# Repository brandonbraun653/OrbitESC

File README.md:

# OrbitESC

Brushless motor controller development environment for STM32-based ESC firmware, a host-side simulator, and a Python GUI/tooling suite.

## Features

- Field-oriented control (FOC)-centric ESC stack with FreeRTOS integration
- STM32F446RE target (embedded) and host simulator build (ChimeraSim)
- Protobuf/Nanopb command and telemetry schema for C/C++ and Python
- Python tools and PyQt5 GUI for monitoring, configuration, and testing
- OrbitCommand: Qt 6/QML C++ desktop console with dark-neon HUD, live plotting, and parameter editing
- CMake presets for embedded and simulator builds

## Project Structure

| Path | Description |
| --- | --- |
| `src/` | C++ sources for firmware, simulator integration, startup, tasks, and libraries. |
| `lib/` | Third-party and in-tree libraries: Aurora, Chimera, ChimeraSim, CMSIS, FreeRTOS, Thor, tinyusb, db. |
| `pyorbit/` | Python package for host tools, GUI (`pyorbit/app`), serial/CAN clients, protobuf stubs. |
| `tools/OrbitCommand/` | Standalone Qt 6/QML C++ desktop console for USB serial, simulator TCP, monitoring, and parameter editing. |
| `scripts/` | Helper scripts: build embedded, generate protobufs, CAN interface setup. |
| `model/` | MATLAB/Simulink models and notebooks related to control algorithms. |
| `CMakePresets.json` | Configure/build presets for embedded and simulator targets. |

---

## Quickstart (Python tooling & GUI)

This repo uses `uv` for Python dependency management. Python 3.11 is required and auto-detected from `pyproject.toml`.

1) Create and sync the environment
```bash
uv venv
uv sync
```

2) Option A: Activate the environment
```bash
source .venv/bin/activate
```

2) Option B: Run one-off commands without activation
```bash
uv run <command>
```

3) Launch the GUI
```bash
uv run python -m pyorbit.app.main
```

Common tasks
```bash
# Run unit tests
uv run pytest

# Type check
uv run mypy

# Lint / Format
uv run flake8
uv run black .
```

Development workflow
- **Add dependencies**: `uv add <package>`
- **Sync/update**: `uv sync`
- **Update lockfile**: `uv lock`

---

## Protobuf/Nanopb workflow

Protobuf definitions live under `src/core/com/proto`. C bindings are generated with Nanopb for the firmware, and Python stubs for `pyorbit`.

Prerequisites
- `protoc` available in PATH
- The repo includes the Nanopb generator under `lib/Aurora/lib/nanopb/...`

Generate all bindings
```bash
cd scripts
./build_proto.sh
```

What it does
- Runs Nanopb to generate C/C++ descriptors into `src/core/com/proto`
- Runs `protoc` to generate Python modules and `.pyi` into `pyorbit/nanopb`

---

## OrbitCommand (Qt 6/QML C++ console)

OrbitCommand is the C++ desktop replacement path for the PyQt GUI. It lives in `tools/OrbitCommand` as a standalone CMake project so it never enters the ARM firmware build.

Build and run:

```bash
cd tools/OrbitCommand
cmake --preset release
cmake --build --preset release
./build/release/OrbitCommand
```

Test all tiers (unit, real-simulator system tests, and Qat GUI E2E):

```bash
uv sync
cmake --preset "OrbitESC Simulator Release"   # from the repository root
cmake --build --preset "OrbitESC Simulator Release"
cd tools/OrbitCommand
cmake --preset release
cmake --build --preset release
ctest --preset release --output-on-failure
```

The system and GUI tiers skip cleanly when the simulator, `qat`, or a display is unavailable. `scripts/test_orbitcommand.sh` wraps the common combinations. See `tools/OrbitCommand/README.md` for prerequisites, test tiers, the Qat object-name contract, protocol notes, simulator connection, and V0 limitations.

---

## Embedded firmware build (STM32F446RE)

The firmware uses CMake presets and GCC ARM toolchain.

Prerequisites
- CMake ≥ 3.16, build-essential toolchain
- Arm GNU Toolchain `arm-none-eabi-*` (see `scripts/install_arm_gcc.sh` or install from Arm)

Configure & build (Debug)
```bash
cmake --preset "OrbitESC_V3 Debug"
cmake --build --preset "OrbitESC_V3 Debug"
```

Configure & build (Release)
```bash
cmake --preset "OrbitESC_V3 Release"
cmake --build --preset "OrbitESC_V3 Release"
```

Artifacts
- Build directories under `build/debug` and `build/release`
- The `OrbitESC` image and map file are produced; a copy of the image is placed under a `sys_image` folder in the preset's runtime output directory

Flashing
- Flashing is board/debugger dependent (ST-Link, J-Link, OpenOCD). Provide your preferred tool or script; a generic OpenOCD flow is recommended.

---

## Simulator build (host)

Build a host-executable with simulated hardware using ChimeraSim.

Host prerequisites (Ubuntu/Debian)
```bash
sudo apt-get update
sudo apt-get install -y build-essential cmake pkg-config libzmq3-dev
```

Configure & build
```bash
cmake --preset "OrbitESC Simulator"
cmake --build --preset "OrbitESC Simulator"
```

Run
```bash
# Example path; adjust if your CMake generator places binaries differently
./build/sim/OrbitESC
```

---

## CAN bus setup (Linux)

Scripts are provided to bring up a `can0` interface at 1 Mbit/s. Root privileges are required.

Open the CAN port
```bash
sudo ./scripts/open_can_port.sh
```

Close the CAN port
```bash
sudo ./scripts/close_can_port.sh
```

Note: Ensure a compatible CAN adapter/driver is present. The Python side uses `python-can`.

---

## Testing & quality checks

All commands can be run with `uv run ...` without activating the venv.

```bash
# Python tests
uv run pytest -q

# Type checks
uv run mypy

# Linting / formatting
uv run flake8
uv run black --check .
```

Pytest is configured to discover tests under `pyorbit/tests`.

OrbitCommand has separate C++ and GUI test tiers:

```bash
scripts/test_orbitcommand.sh              # unit + system + Qat E2E
scripts/test_orbitcommand.sh --unit-only  # no simulator or display required
```

See `tools/OrbitCommand/README.md` for the full tier list, coverage, and sanitizer presets.

---

## Troubleshooting

- CMake cannot find `arm-none-eabi-gcc`: install the Arm GNU Toolchain and ensure it is in PATH.
- Simulator link fails on `zmq`: install `libzmq3-dev` (or the platform equivalent) and reconfigure.
- `protoc: command not found`: install protobuf compiler (`sudo apt-get install -y protobuf-compiler`).
- GUI fails to start: ensure `PyQt5` is installed (it is declared in `pyproject.toml`), then `uv sync` again.

---

## License

MIT. See `LICENSE`.

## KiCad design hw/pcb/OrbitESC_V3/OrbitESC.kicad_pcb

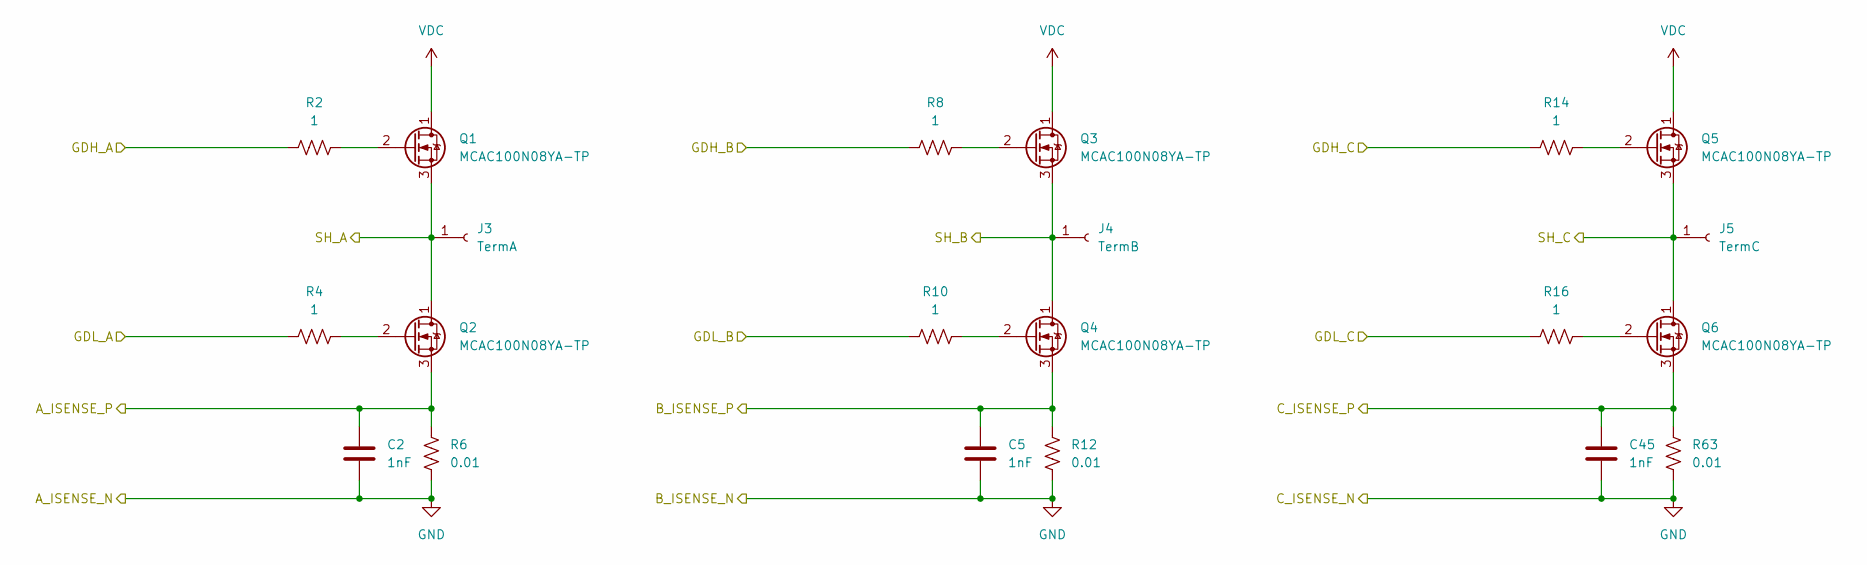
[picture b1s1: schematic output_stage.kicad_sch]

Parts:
C2, C5, C45: 1nF; C_0402_1005Metric; LCSC C1523
J3: TermA; TestPoint_Pad_2.5x2.5mm; DigiKey N/A
J4: TermB; TestPoint_Pad_2.5x2.5mm; DigiKey N/A
J5: TermC; TestPoint_Pad_2.5x2.5mm; DigiKey N/A
Q1, Q2, Q3, Q4, Q5, Q6: MCAC100N08YA-TP; TRANS_BSC076N06NS3-G; DigiKey 353-MCAC100N08YA-TPCT-ND
R2, R4, R8, R10, R14, R16: 1; R_0402_1005Metric; LCSC C25086
R6, R12, R63: 0.01; R_2512_6332Metric; DigiKey CRA2512-FZ-R010ELFCT-ND

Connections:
/Outputs and Shunts/A_ISENSE_P: C2.1, Q2.3 (S), R6.1; also elsewhere on the board
/Outputs and Shunts/B_ISENSE_P: C5.1, Q4.3 (S), R12.1; also elsewhere on the board
/Outputs and Shunts/C_ISENSE_P: C45.1, Q6.3 (S), R63.1; also elsewhere on the board
/Outputs and Shunts/GDH_A: R2.1; also elsewhere on the board
/Outputs and Shunts/GDH_B: R8.1; also elsewhere on the board
/Outputs and Shunts/GDH_C: R14.1; also elsewhere on the board
/Outputs and Shunts/GDL_A: R4.1; also elsewhere on the board
/Outputs and Shunts/GDL_B: R10.1; also elsewhere on the board
/Outputs and Shunts/GDL_C: R16.1; also elsewhere on the board
/Outputs and Shunts/SH_A: J3.1, Q1.3 (S), Q2.1 (D); also elsewhere on the board
/Outputs and Shunts/SH_B: J4.1, Q3.3 (S), Q4.1 (D); also elsewhere on the board
/Outputs and Shunts/SH_C: J5.1, Q5.3 (S), Q6.1 (D); also elsewhere on the board
GND: C2.2, C5.2, C45.2, R6.2, R12.2, R63.2; also elsewhere on the board
unnamed: Q1.2 (G), R2.2
unnamed: Q2.2 (G), R4.2
unnamed: Q3.2 (G), R8.2
unnamed: Q4.2 (G), R10.2
unnamed: Q5.2 (G), R14.2
unnamed: Q6.2 (G), R16.2
VDC: Q1.1 (D), Q3.1 (D), Q5.1 (D); also elsewhere on the board

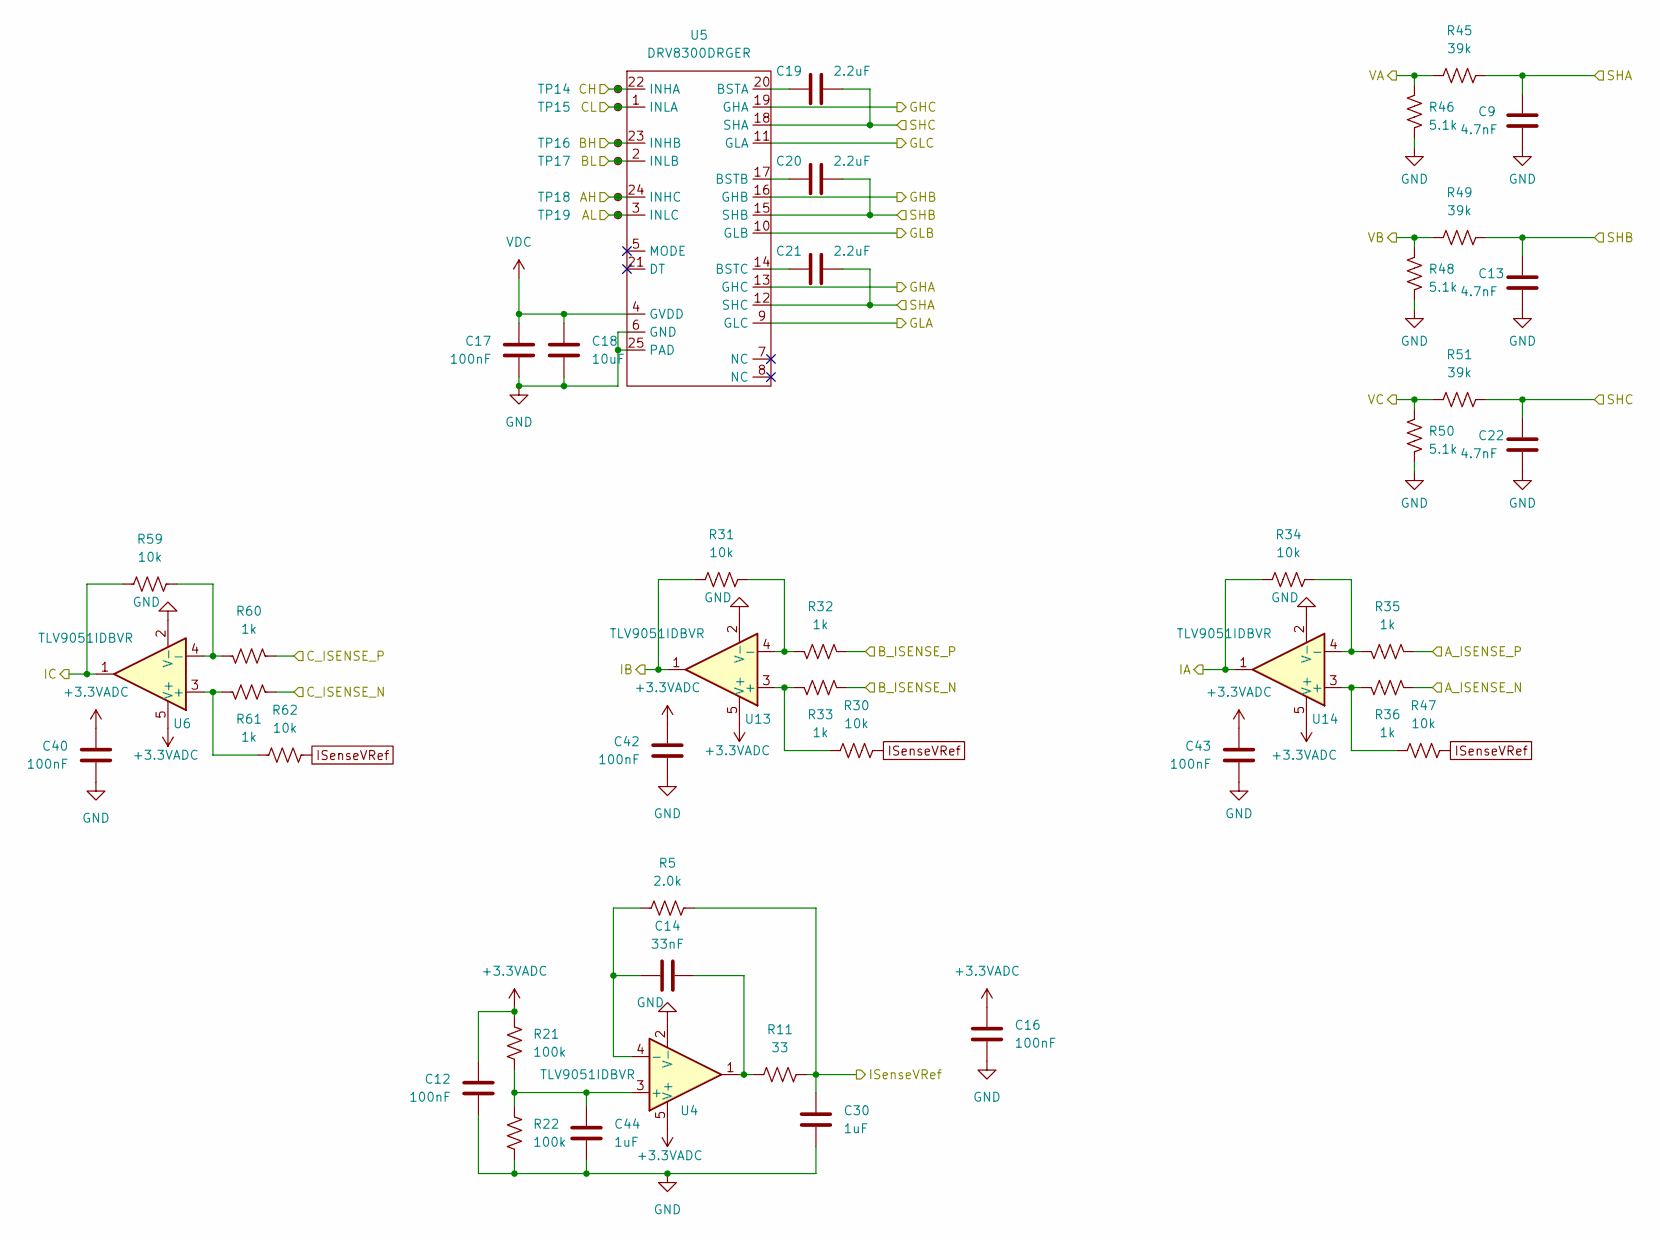
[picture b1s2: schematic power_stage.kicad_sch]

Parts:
C9, C13, C22: 4.7nF; C_0402_1005Metric; LCSC C1538
C12, C16, C17, C40, C42, C43: 100nF; C_0402_1005Metric; LCSC C307331
C14: 33nF; C_0402_1005Metric; LCSC C1585
C18: 10uF; C_0805_2012Metric; LCSC C440198
C19, C20, C21: 2.2uF; C_0805_2012Metric; LCSC C49217
C30, C44: 1uF; C_0402_1005Metric; LCSC C52923
R5: 2.0k; R_0402_1005Metric; LCSC C4109
R11: 33; R_0402_1005Metric; LCSC C25105
R21, R22: 100k; R_0402_1005Metric; LCSC C25741
R30, R31, R34, R47, R59, R62: 10k; R_0402_1005Metric; LCSC C25744
R32, R33, R35, R36, R60, R61: 1k; R_0402_1005Metric; LCSC C11702
R45, R49, R51: 39k; R_0402_1005Metric; LCSC C25783
R46, R48, R50: 5.1k; R_0402_1005Metric; LCSC C25905
TP14: AH; TestPoint_Pad_D1.0mm; DigiKey N/A
TP15: AL; TestPoint_Pad_D1.0mm; DigiKey N/A
TP16: BH; TestPoint_Pad_D1.0mm; DigiKey N/A
TP17: BL; TestPoint_Pad_D1.0mm; DigiKey N/A
TP18: CH; TestPoint_Pad_D1.0mm; DigiKey N/A
TP19: CL; TestPoint_Pad_D1.0mm; DigiKey N/A
U4, U6, U13, U14: TLV9051IDBVR; SOT-23-5; LCSC C1849429
U5: DRV8300DRGER; VQFN-24-1EP_4x4mm_P0.5mm_EP2.45x2.45mm; DigiKey 296-DRV8300DRGERCT-ND

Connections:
+3.3VADC: C12.2, C16.1, C40.1, C42.1, C43.1, R21.2, U4.5 (V+), U6.5 (V+), U13.5 (V+), U14.5 (V+); also elsewhere on the board
/MCU/GATE_DRIVE_AH: TP18.1, U5.24 (INHC); also elsewhere on the board
/MCU/GATE_DRIVE_AL: TP19.1, U5.3 (INLC); also elsewhere on the board
/MCU/GATE_DRIVE_BH: TP16.1, U5.23 (INHB); also elsewhere on the board
/MCU/GATE_DRIVE_BL: TP17.1, U5.2 (INLB); also elsewhere on the board
/MCU/GATE_DRIVE_CH: TP14.1, U5.22 (INHA); also elsewhere on the board
/MCU/GATE_DRIVE_CL: TP15.1, U5.1 (INLA); also elsewhere on the board
/MCU/MOTOR_IA: R34.1, U14.1; also elsewhere on the board
/MCU/MOTOR_IB: R31.1, U13.1; also elsewhere on the board
/MCU/MOTOR_IC: R59.1, U6.1; also elsewhere on the board
/MCU/MOTOR_VA: R45.1, R46.1; also elsewhere on the board
/MCU/MOTOR_VB: R48.1, R49.1; also elsewhere on the board
/MCU/MOTOR_VC: R50.1, R51.1; also elsewhere on the board
/Outputs and Shunts/A_ISENSE_P: R35.1; also elsewhere on the board
/Outputs and Shunts/B_ISENSE_P: R32.1; also elsewhere on the board
/Outputs and Shunts/C_ISENSE_P: R60.1; also elsewhere on the board
/Outputs and Shunts/GDH_A: U5.13 (GHC); also elsewhere on the board
/Outputs and Shunts/GDH_B: U5.16 (GHB); also elsewhere on the board
/Outputs and Shunts/GDH_C: U5.19 (GHA); also elsewhere on the board
/Outputs and Shunts/GDL_A: U5.9 (GLC); also elsewhere on the board
/Outputs and Shunts/GDL_B: U5.10 (GLB); also elsewhere on the board
/Outputs and Shunts/GDL_C: U5.11 (GLA); also elsewhere on the board
/Outputs and Shunts/SH_A: C9.2, C21.2, R45.2, U5.12 (SHC); also elsewhere on the board
/Outputs and Shunts/SH_B: C13.2, C20.2, R49.2, U5.15 (SHB); also elsewhere on the board
/Outputs and Shunts/SH_C: C19.2, C22.2, R51.2, U5.18 (SHA); also elsewhere on the board
GND: C9.1, C12.1, C13.1, C16.2, C17.1, C18.2, C22.1, C30.2, C40.2, C42.2, C43.2, C44.2, R22.1, R33.1, R36.1, R46.2, R48.2, R50.2, R61.1, U4.2 (V-), U5.6 (GND), U5.25 (PAD), U6.2 (V-), U13.2 (V-), U14.2 (V-); also elsewhere on the board
ISenseVRef: C30.1, R5.1, R11.1, R30.2, R47.2, R62.2; also elsewhere on the board
unnamed: C14.2, R11.2, U4.1
unnamed: C44.1, R21.1, R22.2, U4.3 (+)
unnamed: C14.1, R5.2, U4.4 (-)
unnamed: C19.1, U5.20 (BSTA)
unnamed: C20.1, U5.17 (BSTB)
unnamed: C21.1, U5.14 (BSTC)
unnamed: R61.2, R62.1, U6.3 (+)
unnamed: R59.2, R60.2, U6.4 (-)
unnamed: R30.1, R33.2, U13.3 (+)
unnamed: R31.2, R32.2, U13.4 (-)
unnamed: R36.2, R47.1, U14.3 (+)
unnamed: R34.2, R35.2, U14.4 (-)
VDC: C17.2, C18.1, U5.4 (GVDD); also elsewhere on the board

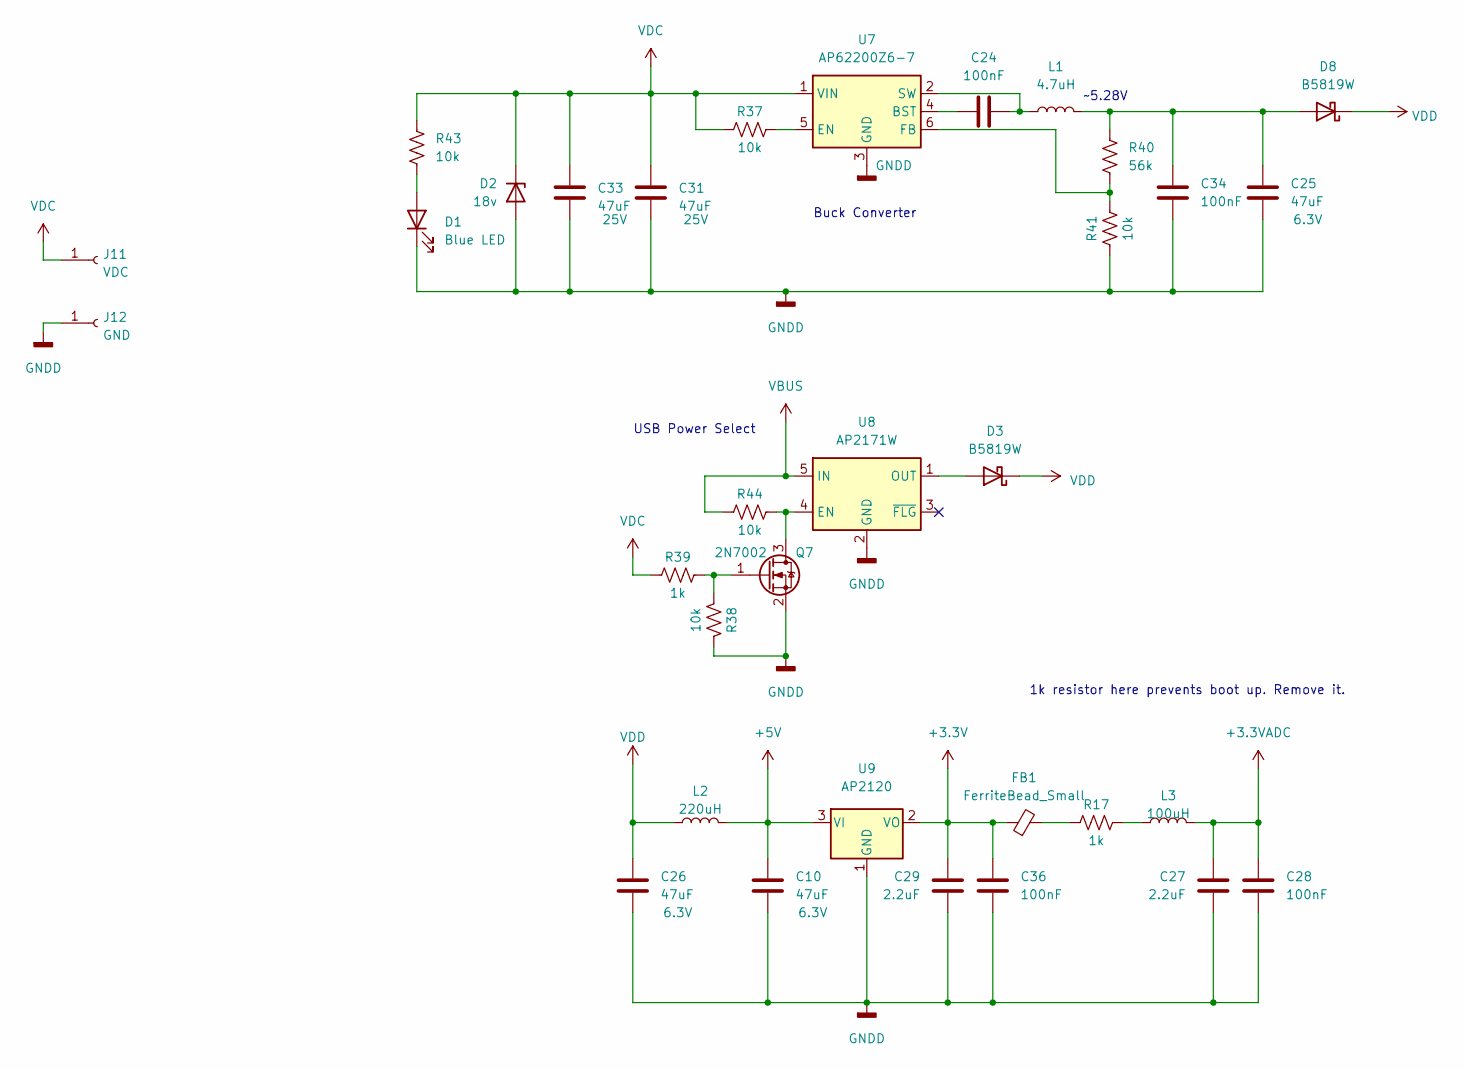
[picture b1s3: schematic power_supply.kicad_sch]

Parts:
C10, C25, C26: 47uF; C_0805_2012Metric; Voltage 6.3V; LCSC C16780
C24, C28, C34, C36: 100nF; C_0402_1005Metric; LCSC C307331
C27, C29: 2.2uF; C_0402_1005Metric; LCSC C12530
C31, C33: 47uF; C_1206_3216Metric; Voltage 25V; DigiKey 445-8047-1-ND
D1: Blue LED; D_0603_1608Metric; LCSC C72041
D2: 18v; D_SMA; DigiKey SMAZ18-FDICT-ND
D3, D8: B5819W; D_SOD-123; LCSC C8598
FB1: FerriteBead_Small; R_0603_1608Metric; LCSC C1002
J11: VDC; TestPoint_Pad_2.5x2.5mm; DigiKey N/A
J12: GND; TestPoint_Pad_2.5x2.5mm; DigiKey N/A
L1: 4.7uH; L_Bourns-SRN6028; DigiKey 587-2100-1-ND
L2: 220uH; L_1812_4532Metric_Pad1.30x3.40mm_HandSolder; DigiKey CM453232-221KLCT-ND
L3: 100uH; L_0805_2012Metric; LCSC C68035
Q7: 2N7002; SOT-23; LCSC C8545
R17, R39: 1k; R_0402_1005Metric; LCSC C11702
R37, R38, R41, R43, R44: 10k; R_0402_1005Metric; LCSC C25744
R40: 56k; R_0402_1005Metric; LCSC C25796
U7: AP62200Z6-7; SOT-563; DigiKey 31-AP62200Z6-7CT-ND
U8: AP2171W; SOT-23-5; DigiKey AP2171WGDICT-ND
U9: AP2120; SOT-23; DigiKey AP2120N-3.3TRG1DICT-ND

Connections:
+3.3V: C29.2, C36.1, FB1.1, U9.2 (VO); also elsewhere on the board
+3.3VADC: C27.2, C28.1, L3.2; also elsewhere on the board
+5V: C10.1, L2.2, U9.3 (VI); also elsewhere on the board
GND: C10.2, C25.2, C26.2, C27.1, C28.2, C29.1, C31.2, C33.2, C34.2, C36.2, D1.1 (K), D2.2 (A), J12.1, Q7.2 (S), R38.1, R41.1, U7.3 (GND), U8.2 (GND), U9.1 (GND); also elsewhere on the board
unnamed: D1.2 (A), R43.2
unnamed: D3.2 (A), U8.1 (OUT)
unnamed: C25.1, C34.1, D8.2 (A), L1.2, R40.1
unnamed: FB1.2, R17.1
unnamed: L3.1, R17.2
unnamed: Q7.3 (D), R44.2, U8.4 (EN)
unnamed: Q7.1 (G), R38.2, R39.2
unnamed: C24.2, U7.4 (BST)
unnamed: R37.2, U7.5 (EN)
unnamed: R40.2, R41.2, U7.6 (FB)
unnamed: C24.1, L1.1, U7.2 (SW)
VBUS: R44.1, U8.5 (IN); also elsewhere on the board
VDC: C31.1, C33.1, D2.1 (K), J11.1, R37.1, R39.1, R43.1, U7.1 (VIN); also elsewhere on the board
VDD: C26.1, D3.1 (K), D8.1 (K), L2.1

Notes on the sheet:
~5.28V
Buck Converter
USB Power Select
1k resistor here prevents boot up. Remove it.

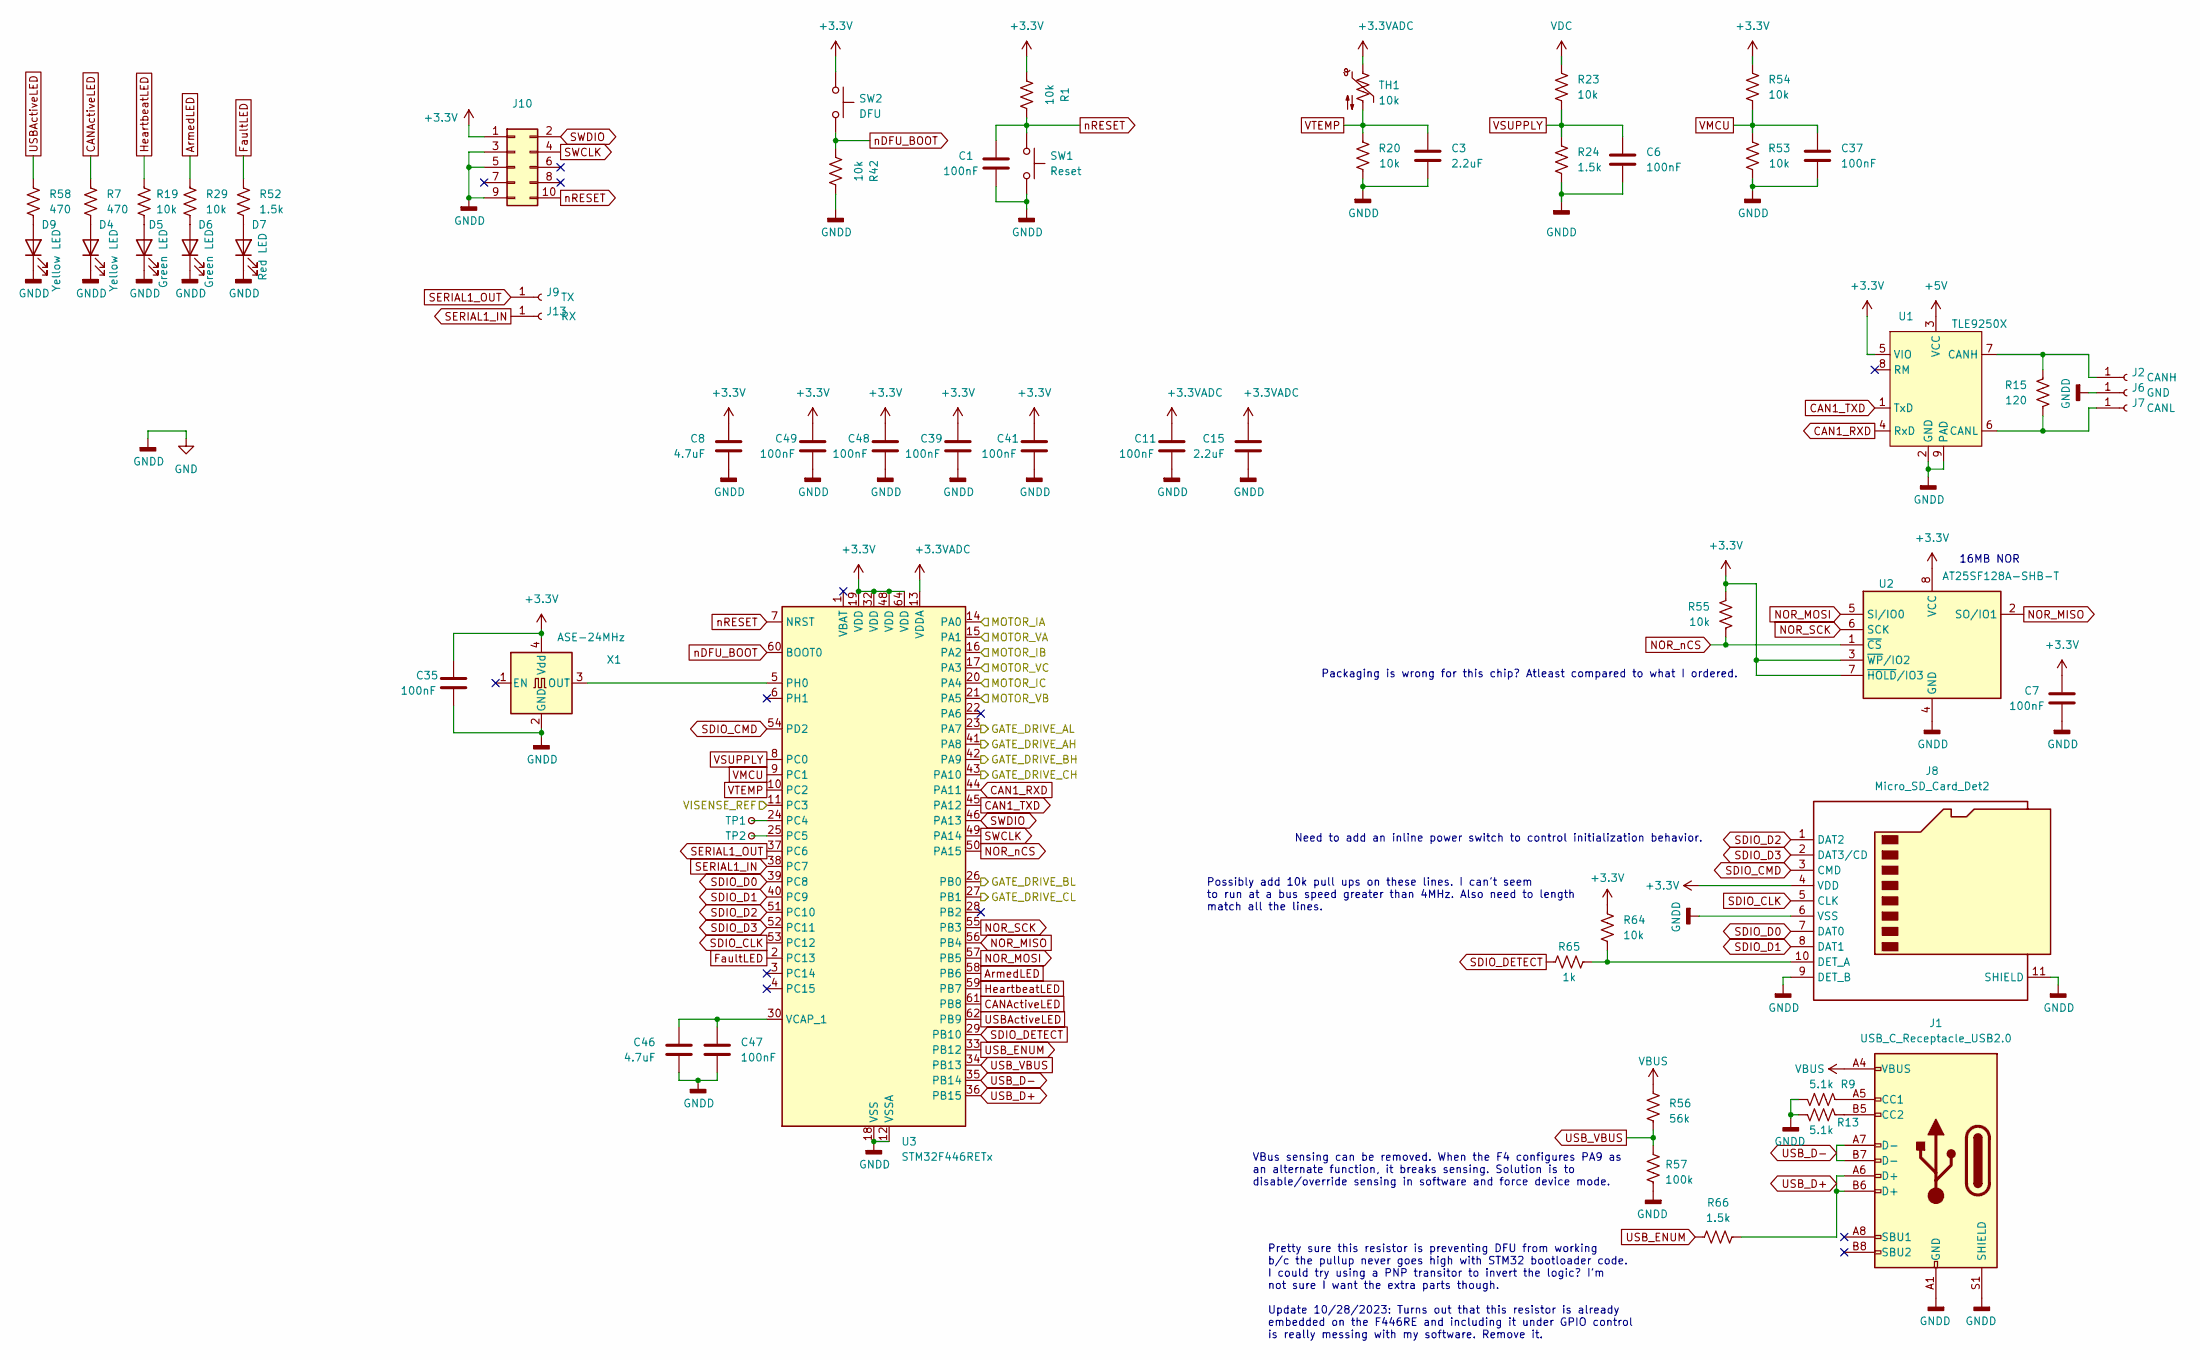
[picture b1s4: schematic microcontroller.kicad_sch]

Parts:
C1, C6, C7, C11, C35, C37, C39, C41, C47, C48, C49: 100nF; C_0402_1005Metric; LCSC C307331
C3, C15: 2.2uF; C_0402_1005Metric; LCSC C12530
C8, C46: 4.7uF; C_0402_1005Metric; LCSC C23733
D4, D9: Yellow LED; D_0603_1608Metric; LCSC C72038
D5, D6: Green LED; D_0603_1608Metric; LCSC C72043
D7: Red LED; D_0603_1608Metric; LCSC C2286
J1: USB_C_Receptacle_USB2.0; USB_C_Receptacle_GCT_USB4085; DigiKey 2073-USB4085-GF-ACT-ND
J2: CANH; TestPoint_Pad_1.5x1.5mm; DigiKey N/A
J6: GND; TestPoint_Pad_1.5x1.5mm; DigiKey N/A
J7: CANL; TestPoint_Pad_1.5x1.5mm; DigiKey N/A
J8: Micro_SD_Card_Det2; microSD_HC_Hirose_DM3D-SF; DigiKey HR1941CT-ND
J9: TX; TestPoint_Pad_1.5x1.5mm; DigiKey N/A
J10: PinHeader_2x05_P1.27mm_Vertical; DigiKey 609-3712-ND
J13: RX; TestPoint_Pad_1.5x1.5mm; DigiKey N/A
R1, R19, R20, R23, R29, R42, R53, R54, R55, R64: 10k; R_0402_1005Metric; LCSC C25744
R7, R58: 470; R_0402_1005Metric; LCSC C25117
R9, R13: 5.1k; R_0402_1005Metric; LCSC C25905
R15: 120; R_0402_1005Metric; LCSC C25079
R24, R52, R66: 1.5k; R_0402_1005Metric; LCSC C25867
R56: 56k; R_0402_1005Metric; LCSC C25796
R57: 100k; R_0402_1005Metric; LCSC C25741
R65: 1k; R_0402_1005Metric; LCSC C11702
SW1: Reset; SW_SPST_EVQP2; DigiKey P11081SCT-ND
SW2: DFU; SW_SPST_EVQP2; DigiKey P11081SCT-ND
TH1: 10k; R_0402_1005Metric; DigiKey 445-2550-1-ND
TP1, TP2: CH; TestPoint_Pad_D1.0mm; DigiKey N/A
U1: TLE9250X; HVSON-8-1EP_3x3mm_P0.65mm_EP1.6x2.4mm; DigiKey 448-TLE9250XLEXUMA1CT-ND
U2: AT25SF128A-SHB-T; SOIC-8_3.9x4.9mm_P1.27mm; DigiKey 1265-1348-1-ND
U3: STM32F446RETx; LQFP-64_10x10mm_P0.5mm; LCSC C69336
X1: ASE-24MHz; Oscillator_SMD_Abracon_ASE-4Pin_3.2x2.5mm; DigiKey 535-ASE-24.000MHZ-L-C-TCT-ND

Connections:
+3.3V: C7.2, C8.2, C35.2, C39.2, C41.2, C48.2, C49.2, J8.4 (VDD), J10.1, R1.2, R54.2, R55.2, R64.2, SW2.1, U1.5 (VIO), U2.3 (~WP/IO2), U2.7 (~HOLD/IO3), U2.8 (VCC), U3.19 (VDD), U3.32 (VDD), U3.48 (VDD), U3.64 (VDD), X1.4 (Vdd); also elsewhere on the board
+3.3VADC: C11.2, C15.2, TH1.1, U3.13 (VDDA); also elsewhere on the board
+5V: U1.3 (VCC); also elsewhere on the board
/MCU/GATE_DRIVE_AH: U3.41 (PA8); also elsewhere on the board
/MCU/GATE_DRIVE_AL: U3.23 (PA7); also elsewhere on the board
/MCU/GATE_DRIVE_BH: U3.42 (PA9); also elsewhere on the board
/MCU/GATE_DRIVE_BL: U3.26 (PB0); also elsewhere on the board
/MCU/GATE_DRIVE_CH: U3.43 (PA10); also elsewhere on the board
/MCU/GATE_DRIVE_CL: U3.27 (PB1); also elsewhere on the board
/MCU/MOTOR_IA: U3.14 (PA0); also elsewhere on the board
/MCU/MOTOR_IB: U3.16 (PA2); also elsewhere on the board
/MCU/MOTOR_IC: U3.20 (PA4); also elsewhere on the board
/MCU/MOTOR_VA: U3.15 (PA1); also elsewhere on the board
/MCU/MOTOR_VB: U3.21 (PA5); also elsewhere on the board
/MCU/MOTOR_VC: U3.17 (PA3); also elsewhere on the board
ArmedLED: R29.1, U3.58 (PB6)
CAN1_RXD: U1.4 (RxD), U3.44 (PA11)
CAN1_TXD: U1.1 (TxD), U3.45 (PA12)
CANActiveLED: R7.1, U3.61 (PB8)
FaultLED: R52.1, U3.2 (PC13)
GND: C1.1, C3.1, C6.2, C7.1, C8.1, C11.1, C15.1, C35.1, C37.2, C39.1, C41.1, C46.1, C47.2, C48.1, C49.1, D4.1 (K), D5.1 (K), D6.1 (K), D7.1 (K), D9.1 (K), J1.A1 (GND), J1.A12 (GND), J1.B1 (GND), J1.B12 (GND), J1.S1 (SHIELD), J6.1, J8.6 (VSS), J8.9 (DET_B), J8.11 (SHIELD), J10.3, J10.5, J10.9, R9.1, R13.2, R20.1, R24.2, R42.1, R53.1, R57.2, SW1.2, U1.2 (GND), U1.9 (PAD), U2.4 (GND), U3.12 (VSSA), U3.18 (VSS), U3.31 (VSS), U3.47 (VSS), U3.63 (VSS), X1.2 (GND); also elsewhere on the board
HeartbeatLED: R19.1, U3.59 (PB7)
ISenseVRef: U3.11 (PC3); also elsewhere on the board
NOR_MISO: U2.2 (SO/IO1), U3.56 (PB4)
NOR_MOSI: U2.5 (SI/IO0), U3.57 (PB5)
NOR_SCK: U2.6 (SCK), U3.55 (PB3)
NOR_nCS: R55.1, U2.1 (~CS), U3.50 (PA15)
unnamed: D4.2 (A), R7.2
unnamed: D5.2 (A), R19.2
unnamed: D6.2 (A), R29.2
unnamed: D7.2 (A), R52.2
unnamed: D9.2 (A), R58.2
unnamed: J1.A5 (CC1), R9.2
unnamed: J1.B5 (CC2), R13.1
unnamed: J2.1, R15.2, U1.7 (CANH)
unnamed: J7.1, R15.1, U1.6 (CANL)
unnamed: J8.10 (DET_A), R64.1, R65.2
unnamed: TP1.1, U3.24 (PC4)
unnamed: TP2.1, U3.25 (PC5)
unnamed: U3.5 (PH0), X1.3 (OUT)
unnamed: C46.2, C47.1, U3.30 (VCAP_1)
SDIO_CLK: J8.5 (CLK), U3.53 (PC12)
SDIO_CMD: J8.3 (CMD), U3.54 (PD2)
SDIO_D0: J8.7 (DAT0), U3.39 (PC8)
SDIO_D1: J8.8 (DAT1), U3.40 (PC9)
SDIO_D2: J8.1 (DAT2), U3.51 (PC10)
SDIO_D3: J8.2 (DAT3/CD), U3.52 (PC11)
SDIO_DETECT: R65.1, U3.29 (PB10)
SERIAL1_IN: J13.1, U3.38 (PC7)
SERIAL1_OUT: J9.1, U3.37 (PC6)
SWCLK: J10.4, U3.49 (PA14)
SWDIO: J10.2, U3.46 (PA13)
USBActiveLED: R58.1, U3.62 (PB9)
USB_D+: J1.A6 (D+), J1.B6 (D+), R66.2, U3.36 (PB15)
USB_D-: J1.A7 (D-), J1.B7 (D-), U3.35 (PB14)
USB_ENUM: R66.1, U3.33 (PB12)
USB_VBUS: R56.2, R57.1, U3.34 (PB13)
VBUS: J1.A4 (VBUS), J1.A9 (VBUS), J1.B4 (VBUS), J1.B9 (VBUS), R56.1; also elsewhere on the board
VDC: R23.2; also elsewhere on the board
VMCU: C37.1, R53.2, R54.1, U3.9 (PC1)
VSUPPLY: C6.1, R23.1, R24.1, U3.8 (PC0)
VTEMP: C3.2, R20.2, TH1.2, U3.10 (PC2)
nDFU_BOOT: R42.2, SW2.2, U3.60 (BOOT0)
nRESET: C1.2, J10.10, R1.1, SW1.1, U3.7 (NRST)

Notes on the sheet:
Need to add an inline power switch to control initialization behavior.
Packaging is wrong for this chip? Atleast compared to what I ordered.
Possibly add 10k pull ups on these lines. I can't seem to run at a bus speed greater than 4MHz. Also need to length match all the lines.
Pretty sure this resistor is preventing DFU from working b/c the pullup never goes high with STM32 bootloader code. I could try using a PNP transitor to invert the logic? I'm not sure I want the extra parts though. Update 10/28/2023: Turns out that this resistor is already embedded on the F446RE an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
VBus sensing can be removed. When the F4 configures PA9 as an alternate function, it breaks sensing. Solution is to disable/override sensing in software and force device mode.
16MB NOR

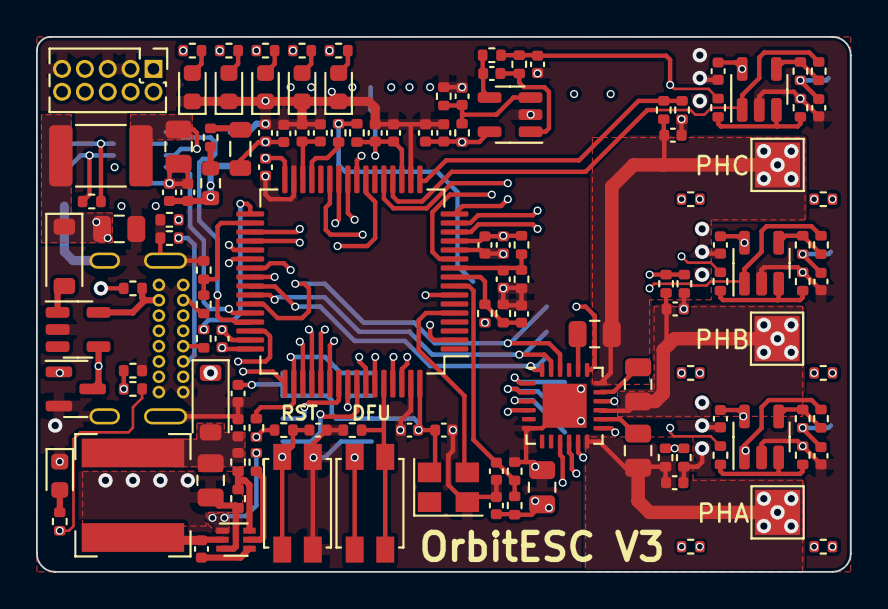
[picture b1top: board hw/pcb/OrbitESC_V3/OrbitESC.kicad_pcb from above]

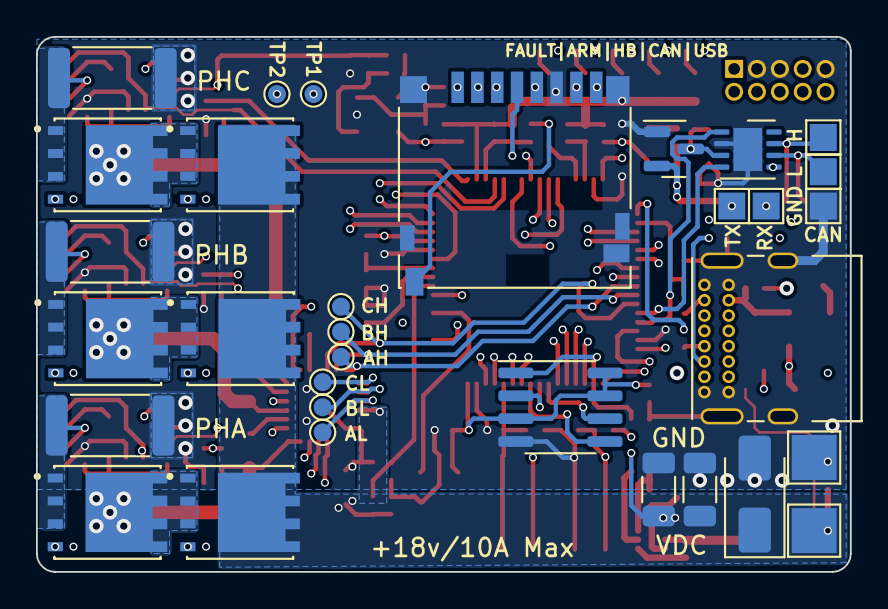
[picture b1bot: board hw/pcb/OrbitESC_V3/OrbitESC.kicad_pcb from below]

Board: 8 copper layers, 45.2 x 29.7 mm, 161 parts (32 on the bottom side), 106 nets.

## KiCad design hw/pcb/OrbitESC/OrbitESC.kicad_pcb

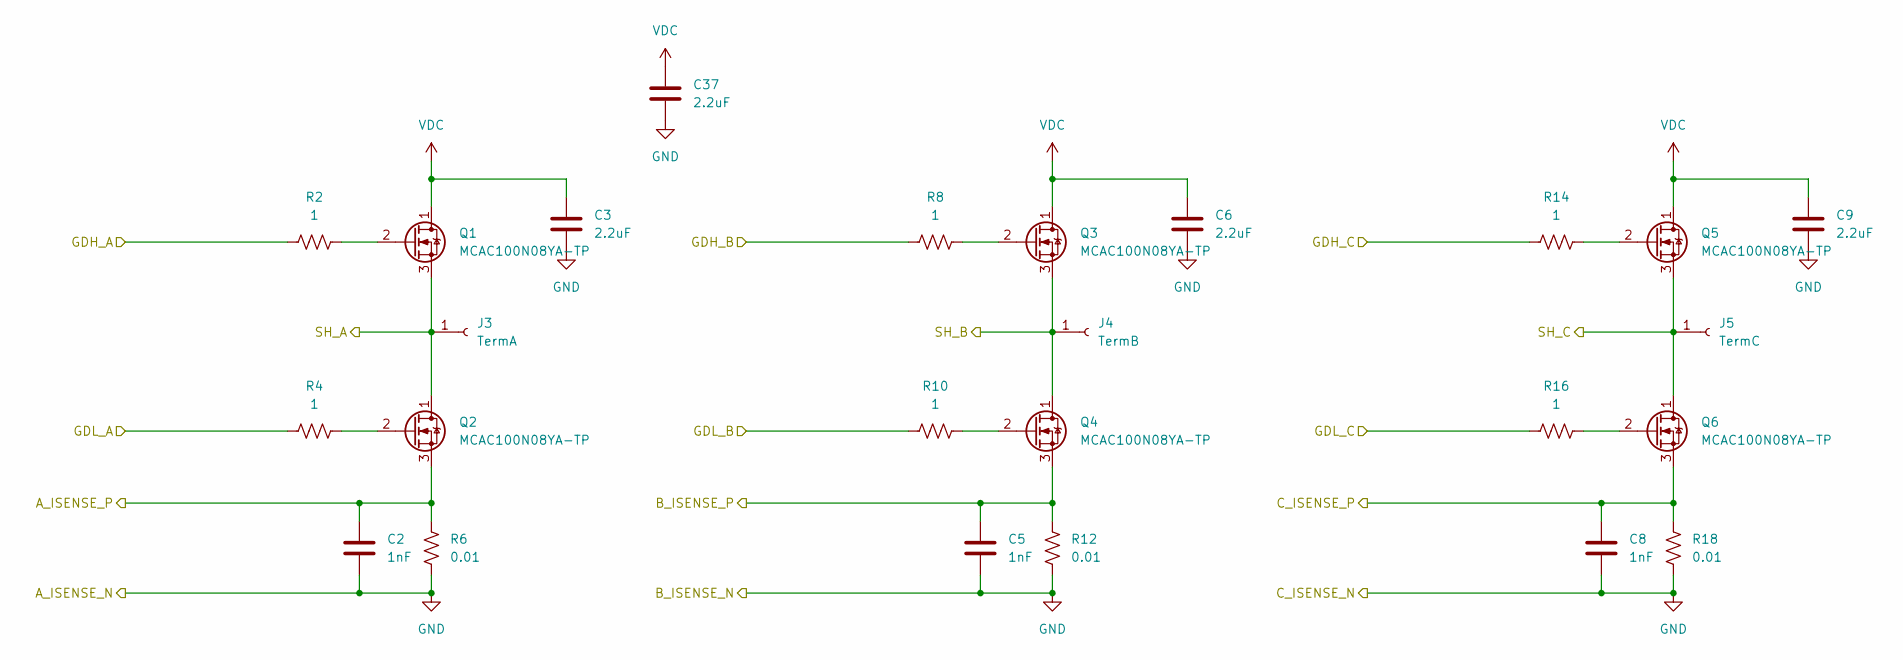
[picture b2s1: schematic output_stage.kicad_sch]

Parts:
C2, C5, C8: 1nF; C_0402_1005Metric; LCSC C1523
C3, C6, C9, C37: 2.2uF; C_0805_2012Metric; LCSC C49217
J3: TermA; TestPoint_Pad_4.0x4.0mm; DigiKey N/A
J4: TermB; TestPoint_Pad_4.0x4.0mm; DigiKey N/A
J5: TermC; TestPoint_Pad_4.0x4.0mm; DigiKey N/A
Q1, Q2, Q3, Q4, Q5, Q6: MCAC100N08YA-TP; TRANS_BSC076N06NS3-G; DigiKey 353-MCAC100N08YA-TPCT-ND
R2, R4, R8, R10, R14, R16: 1; R_0402_1005Metric; LCSC C25086
R6, R12, R18: 0.01; R_2512_6332Metric; DigiKey CRA2512-FZ-R010ELFCT-ND

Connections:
/Outputs and Shunts/A_ISENSE_P: C2.1, Q2.3 (S), R6.1; also elsewhere on the board
/Outputs and Shunts/B_ISENSE_P: C5.1, Q4.3 (S), R12.1; also elsewhere on the board
/Outputs and Shunts/C_ISENSE_P: C8.1, Q6.3 (S), R18.1; also elsewhere on the board
/Outputs and Shunts/GDH_A: R2.1; also elsewhere on the board
/Outputs and Shunts/GDH_B: R8.1; also elsewhere on the board
/Outputs and Shunts/GDH_C: R14.1; also elsewhere on the board
/Outputs and Shunts/GDL_A: R4.1; also elsewhere on the board
/Outputs and Shunts/GDL_B: R10.1; also elsewhere on the board
/Outputs and Shunts/GDL_C: R16.1; also elsewhere on the board
/Outputs and Shunts/SH_A: J3.1, Q1.3 (S), Q2.1 (D); also elsewhere on the board
/Outputs and Shunts/SH_B: J4.1, Q3.3 (S), Q4.1 (D); also elsewhere on the board
/Outputs and Shunts/SH_C: J5.1, Q5.3 (S), Q6.1 (D); also elsewhere on the board
GND: C2.2, C3.2, C5.2, C6.2, C8.2, C9.2, C37.2, R6.2, R12.2, R18.2; also elsewhere on the board
unnamed: Q1.2 (G), R2.2
unnamed: Q2.2 (G), R4.2
unnamed: Q3.2 (G), R8.2
unnamed: Q4.2 (G), R10.2
unnamed: Q5.2 (G), R14.2
unnamed: Q6.2 (G), R16.2
VDC: C3.1, C6.1, C9.1, C37.1, Q1.1 (D), Q3.1 (D), Q5.1 (D); also elsewhere on the board
